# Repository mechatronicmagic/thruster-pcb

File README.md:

- [Repository Info](#orgcf761ff)
- [Images](#orga1b146e)
- [Schematic](#org2f8730d)
- [PCB](#orgee0fed7)
- [Bill of Materials](#org8738594)
- [Development](#org028dfc6)

    <!-- This file is generated automatically from metadata -->
    <!-- File edits may be overwritten! -->

# Repository Info

-   Project Name: thruster-pcb
-   Synopsis:
-   Documentation Version: 1.0.0
-   Pcb Version: 1.0
-   Enclosure Version: 1.0
-   Supplemental BOM Version: 1.0
-   Release Date: 2025-02-19
-   Creation Date: 2025-01-04
-   Kicad Version: 7.0.11
-   License: GPL-3.0h
-   URL: <https://github.com/mechatronicmagic/thruster-pcb>
-   Author: Peter Polidoro
-   Email: peter@polidoro.io
-   Copyright: 2025 Mechatronic Magic
-   References:
    -   [Servo Control](https://en.wikipedia.org/wiki/Servo_control)
    -   [SB2264MG Servo](https://www.savoxusa.com/products/savsb2264mg-low-profile-hv-brushless-servo)
    -   [PCA9685](https://www.nxp.com/products/power-management/lighting-driver-and-controller-ics/led-drivers/16-channel-12-bit-pwm-fm-plus-ic-bus-led-driver:PCA9685)
    -   [nRF52840 Express](https://www.adafruit.com/product/4062)

# Images

# Schematic

[./documentation/schematic/thruster-pcb.pdf](./documentation/schematic/thruster-pcb.pdf)

# PCB

# Bill of Materials

## Board

| Item | Synopsis                          | Manufacturer Part Number | Manufacturer                         | Quantity | Reference(s)                       | Package             |
|---- |--------------------------------- |------------------------ |------------------------------------ |-------- |---------------------------------- |------------------- |
| 1    | 50V 3.3uF                         | FS32X335K500EGG          | PSA(Prosperity Dielectrics)          | 1        | C301                               | 1210                |
| 2    | CAP CER 0.1UF 100V X5R            | GRM155R62A104KE14D       | Murata Electronics                   | 5        | C302 C401 C501 C502 C503           | 0402                |
| 3    | CAP CER 1UF 25V X5R               | GRT155R61E105KE01D       | Murata Electronics                   | 2        | C303 C304                          | 0402                |
| 4    | CAP CER 47UF 10V X5R              | CGA0805X5R476M100MT      | HRE                                  | 7        | C305 C504 C505 C506 C507 C508 C509 | 0805                |
| 5    | DIODE SCHOTTKY 20V 1A             | MBR120VLSFT1G            | onsemi                               | 1        | D401                               | SOD-123FL           |
| 6    | MAXIBR M 03POS RA A SMT BK        | 284052-E                 | TE Connectivity                      | 7        | J301 J501 J502 J503 J504 J505 J506 |                     |
| 7    | RES SMD 1.8K OHM 5% 100mW         | ERJ2GEJ182X              | PANASONIC                            | 2        | R401 R402                          | 0402                |
| 8    | 1 Digit SPST 24V 25mA DIP         | EM-01KP                  | Korean Hroparts Elec                 | 1        | SW401                              | SMD,2.5x6mm         |
| 9    | DC-DC 5V 600mA Output 3-65V Input | TPSM365R6V5RDNR          | Texas Instruments                    | 1        | U301                               | QFN-11(3.5x4.5)     |
| 10   | IC SWITCH DEBOUNCER               | MAX6816EUS+T             | Analog Devices Inc./Maxim Integrated | 1        | U401                               | SOT-143             |
| 11   | IC LED DRVR LIN PWM 25MA          | PCA9685BS,118            | NXP Semicon                          | 1        | U501                               | SOT-788-1           |
| 12   | IC TRANSLTR BIDIRECTIONAL         | TXS0108ERGYR             | Texas Instruments                    | 1        | U502                               | VQFN-20-EP(3.7x4.7) |

## Supplemental

| Item | Synopsis                                                            | Manufacturer Part Number | Manufacturer | Quantity | Cost  | Total |
|---- |------------------------------------------------------------------- |------------------------ |------------ |-------- |----- |----- |
| 1    | Adafruit Feather nRF52840 Express                                   | 4062                     | adafruit     | 1        | 24.95 | 24.95 |
| 2    | NiMH Battery (6V, 2700mAh, 2-Pos TJC8 Power Connector [MH-FC], 6-1) | 3100-0006-0001           | servocity    | 1        | 14.99 | 14.99 |
|      | Supplemental BOM Version: 1.0                                       |                          |              |          | Total | 39.94 |

# Development

## Install Guix

[Install Guix](https://guix.gnu.org/manual/en/html_node/Binary-Installation.html)

## Generate Output from KiCad

### Remove previous versions

```sh
rm -rf ./documentation/3dmodels/* && rm -rf ./documentation/bom/* && rm -rf ./documentation/fabrication/* && rm -rf ./documentation/pcb/* && rm -rf ./documentation/schematic/*pcb
```

### Images

1.  3D Viewer

    Output directory: ../documentation/pcb
    
    -   pcb.png
    -   top.png
    -   bottom.png
    -   front.png
    -   back.png
    -   left.png
    -   right.png

2.  Trim

        make trimmed-images

3.  Schematic PDF

    File -> Plot
    
    Output directory: ../documentation/schematic
    
    Plot All Pages
    
    -   Output format PDF
    -   Page Size = Schematic size
    -   Plot drawing sheet
    -   Output mode = Color
    -   Color theme = KiCad Default
    -   Default line width = 0.006 in

4.  Schematic SVG

    File -> Plot
    
    Output directory: ../documentation/schematic
    
    Plot All Pages
    
    -   Output format SVG
    -   Page Size = Schematic size
    -   Plot drawing sheet
    -   Output mode = Color
    -   Color theme = Solarized Light
    -   Default line width = 0.012 in

5.  PCB SVG

    Add Edge.Cuts, holes, and dimensions to User.Drawings
    
    File -> Plot
    
    Output directory: ../documentation/pcb
    
    -   Plot format SVG
    -   Include Layers
        -   User.Drawings
        -   F.Silkscreen
        -   B.Silkscreen
        -   F.Fab
        -   B.Fab
    -   Plot on All Layers
        -   Edge.Cuts
    -   Plot footprint values
    -   Plot reference designators
    -   SVG Options
        -   Precision = 4
        -   Output mode = color
    
        make cropped-svg

### Fabrication Files

1.  Gerbers

    File -> Fabrication Outputs -> Gerbers (.gbr)
    
    Output directory: ../documentation/fabrication/gerbers
    
    Include Layers:
    
    -   F.Cu
    -   F.Paste
    -   F.Silks
    -   F.Mask
    -   F.Fab
    -   B.Cu
    -   B.Paste
    -   B.Silks
    -   B.Mask
    -   B.Fab
    -   Edge.Cuts - (contain the board outline/cutouts.)
    -   In1.Cu, In2.Cu … - (needed for 4/6 layer designs.)
    
    Options:
    
    -   Select Plot reference designators, otherwise designators will not appear on silkscreen layers.
    -   Select Check zone fills before plotting
    -   Select Use Protel filename extensions, this is recommended as JLCPCB prefers Protel filename extensions.
    -   Select Subtract soldermask from silkscreen, this ensures no silkscreen on pads.
    -   Coordinate format 4.6 unit mm

2.  Drill and Map Files

    Output directory: ../documentation/fabrication/gerbers
    
    Options:
    
    -   Excellon drill file format
    -   Check Use alternate drill mode for "Oval Holes Drill Mode".
    -   Check Absolute for "Drill Origin".
    -   Check Millimeters for "Drill Units".
    -   Check Decimal format for "Zeros Format".
    -   Gerber X2 map file format
    
    Zip gerber files
    
        zip ./documentation/fabrication/gerbers.zip ./documentation/fabrication/gerbers/*

3.  BOM

    Generate BOM from schematic editor using blank command line to create bom xml file.

4.  POS

    File -> Fabrication Outputs -> Component Placement (.pos)
    
    Output directory: ../documentation/fabrication/
    
    Settings:
    
    -   Format = CSV
    -   Units = Millimeters
    -   Files = Single file for board
    -   Do not use drill/place file origin
    
    Modify pos files:
    
    -   Ref -> Designator
    -   PosX -> Mid X
    -   PosY -> Mid Y
    -   Rot -> Rotation
    -   Side -> Layer

5.  Step

    File -> Export -> Step
    
    Output directory: ../documentation/3dmodels/pcb.step
    
    -   Drill/place file origin
    -   Overwrite old file
    -   Standard Board outline chaining tolerance

## Edit metadata.org

    make metadata-edits

## Tangle metadata.org

    make metadata

## Edit project

    make kicad-edits
    exit

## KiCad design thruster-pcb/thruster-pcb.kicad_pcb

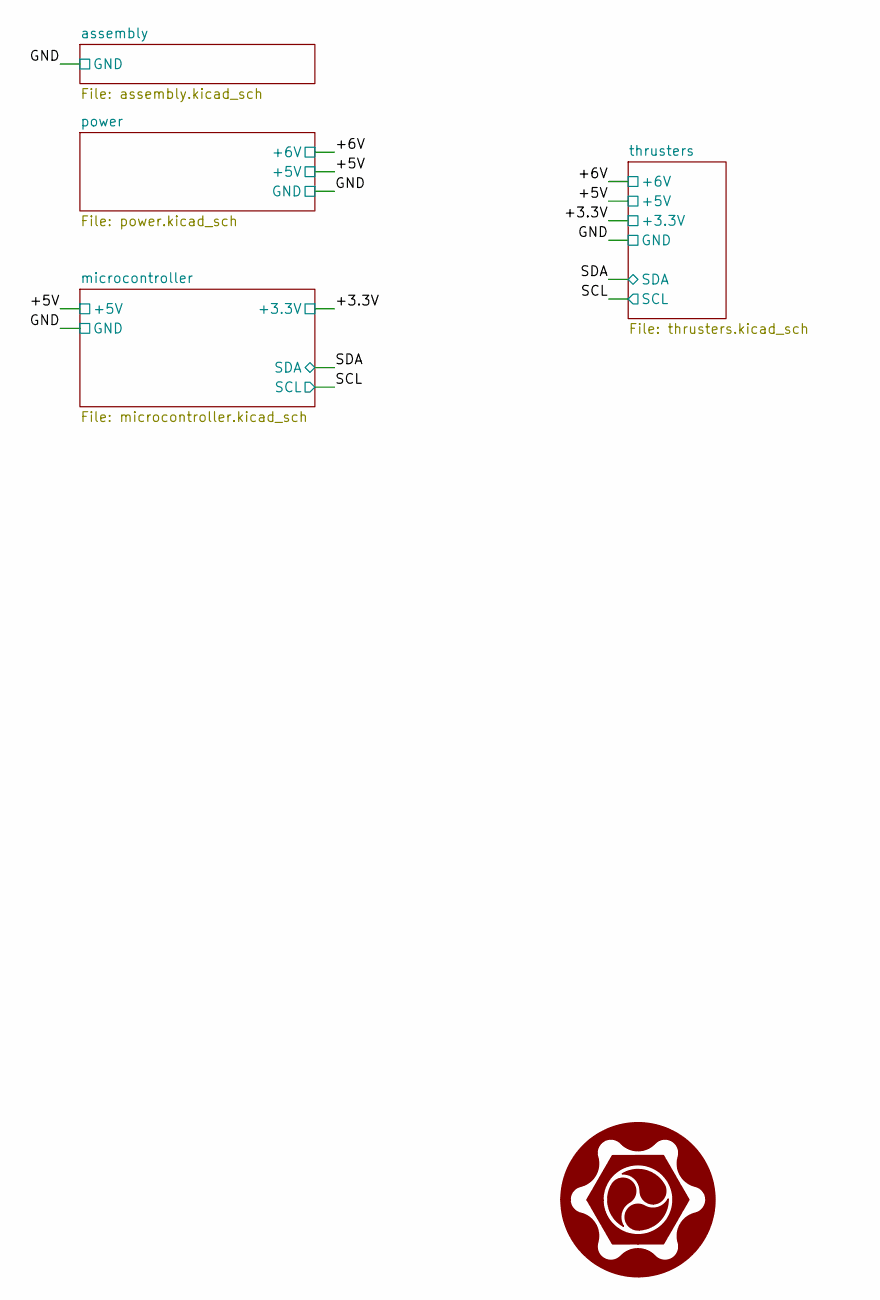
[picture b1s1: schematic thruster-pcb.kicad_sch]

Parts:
G101: LOGO-10mm; logo-white-fg-black-bg-10mm

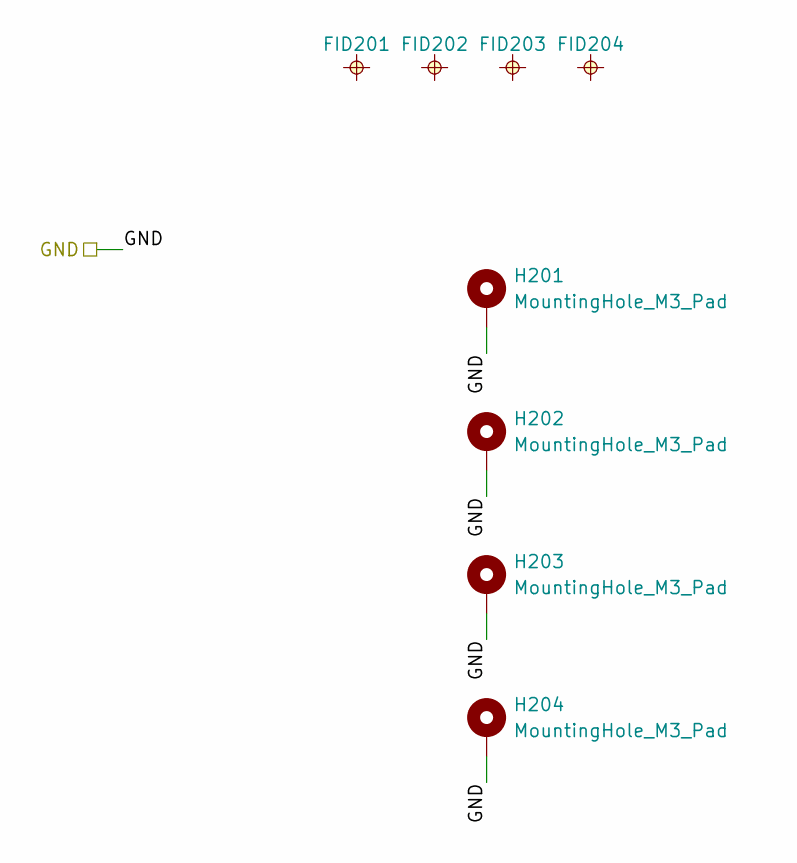
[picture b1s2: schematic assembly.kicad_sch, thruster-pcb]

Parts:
FID201, FID202, FID203, FID204: FIDUCIAL_0.5mm_MASK1mm; FIDUCIAL_0.5mm_Mask1mm
H201, H202, H203, H204: MountingHole_M3_Pad; MountingHole_3.2mm_M3_Pad

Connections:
/GND: H201.1, H202.1, H203.1, H204.1; also elsewhere on the board

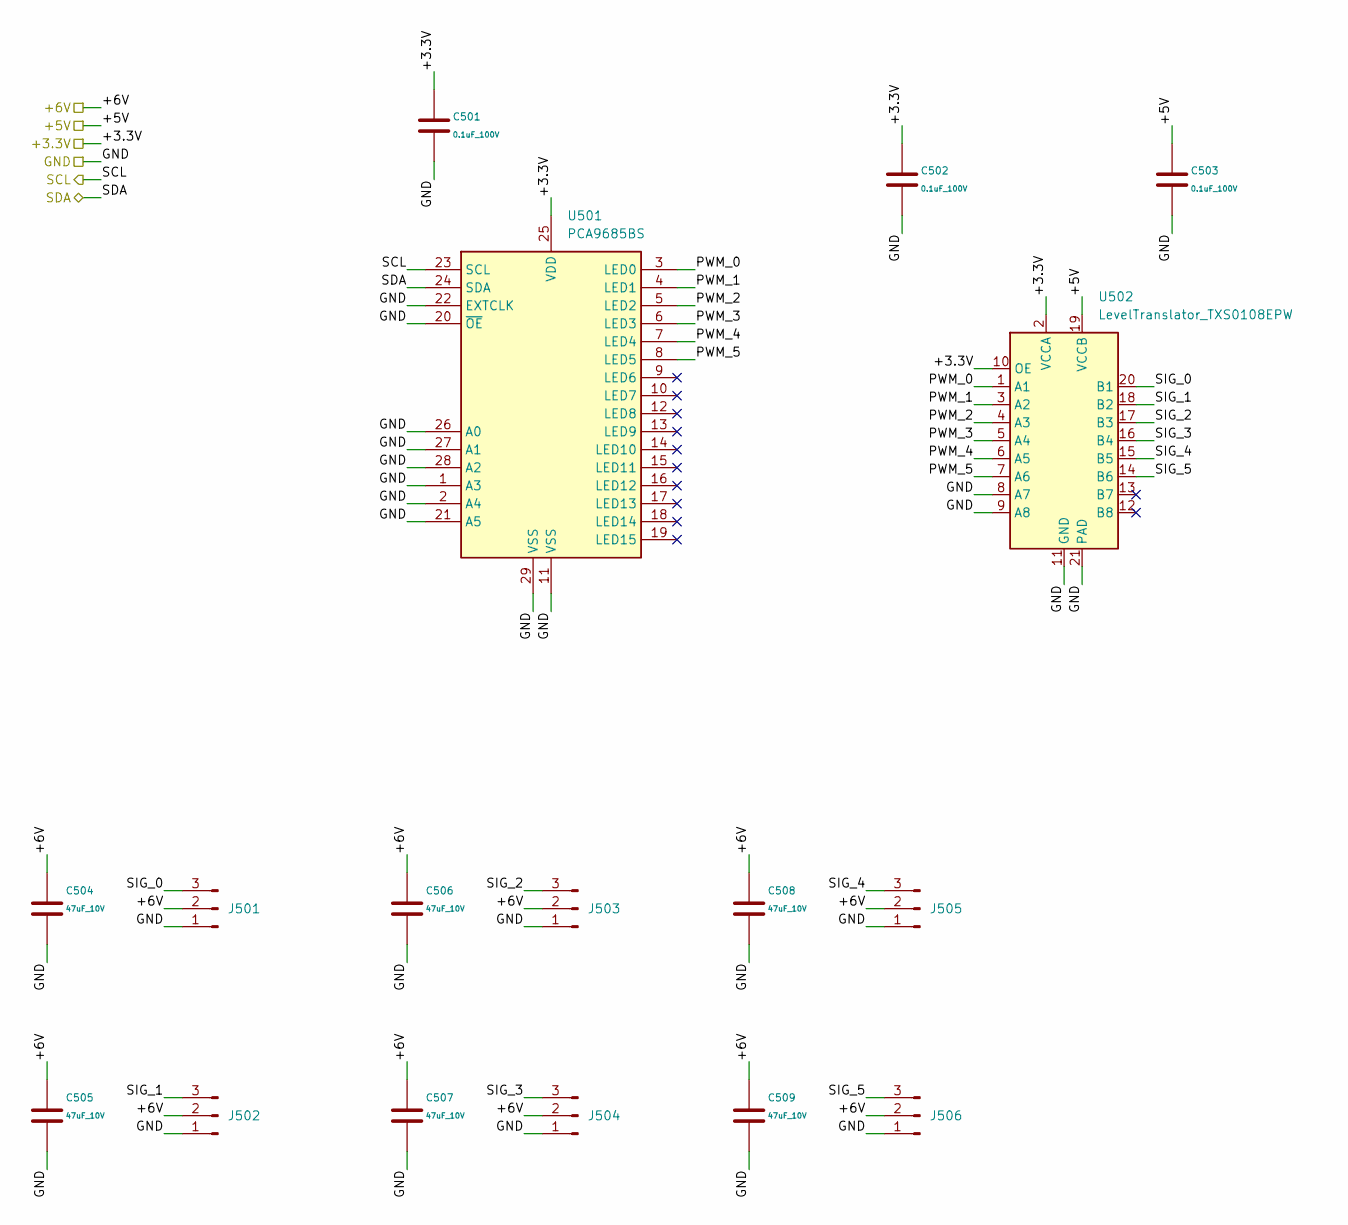
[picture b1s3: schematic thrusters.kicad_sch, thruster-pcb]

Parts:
C501, C502, C503: 0.1uF_100V; C_0402_1005Metric; Manufacturer Part Number GRM155R62A104KE14D; LCSC C162178
C504, C505, C506, C507, C508, C509: 47uF_10V; C_0805_2012Metric; Manufacturer Part Number CGA0805X5R476M100MT; LCSC C6119904
J501, J502, J503, J504, J505, J506: Conn_TERM_HDR_01x03_Pin_3.5mm_Horizontal; Connector_Header_1x03_P2.54mm_Horizontal_SMD_284052-E; Manufacturer Part Number 284052-E; LCSC C17355078
U501: PCA9685BS; QFN-28-1EP_6x6mm_P0.65mm_EP4.25x4.25mm; Manufacturer Part Number PCA9685BS,118; LCSC C5191634
U502: LevelTranslator_TXS0108EPW; IC_TXS0108ERGYR; Manufacturer Part Number TXS0108ERGYR; LCSC C90706

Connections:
/+3.3V: C501.1, C502.1, U501.25 (VDD), U502.2 (VCCA), U502.10 (OE); also elsewhere on the board
/+5V: C503.1, U502.19 (VCCB); also elsewhere on the board
/+6V: C504.1, C505.1, C506.1, C507.1, C508.1, C509.1, J501.2, J502.2, J503.2, J504.2, J505.2, J506.2; also elsewhere on the board
/GND: C501.2, C502.2, C503.2, C504.2, C505.2, C506.2, C507.2, C508.2, C509.2, J501.1, J502.1, J503.1, J504.1, J505.1, J506.1, U501.1 (A3), U501.2 (A4), U501.11 (VSS), U501.20 (~OE), U501.21 (A5), U501.22 (EXTCLK), U501.26 (A0), U501.27 (A1), U501.28 (A2), U501.29 (VSS), U502.8 (A7), U502.9 (A8), U502.11 (GND), U502.21 (PAD); also elsewhere on the board
/SCL: U501.23 (SCL); also elsewhere on the board
/SDA: U501.24 (SDA); also elsewhere on the board
/thrusters/PWM_0: U501.3 (LED0), U502.1 (A1)
/thrusters/PWM_1: U501.4 (LED1), U502.3 (A2)
/thrusters/PWM_2: U501.5 (LED2), U502.4 (A3)
/thrusters/PWM_3: U501.6 (LED3), U502.5 (A4)
/thrusters/PWM_4: U501.7 (LED4), U502.6 (A5)
/thrusters/PWM_5: U501.8 (LED5), U502.7 (A6)
/thrusters/SIG_0: J501.3, U502.20 (B1)
/thrusters/SIG_1: J502.3, U502.18 (B2)
/thrusters/SIG_2: J503.3, U502.17 (B3)
/thrusters/SIG_3: J504.3, U502.16 (B4)
/thrusters/SIG_4: J505.3, U502.15 (B5)
/thrusters/SIG_5: J506.3, U502.14 (B6)

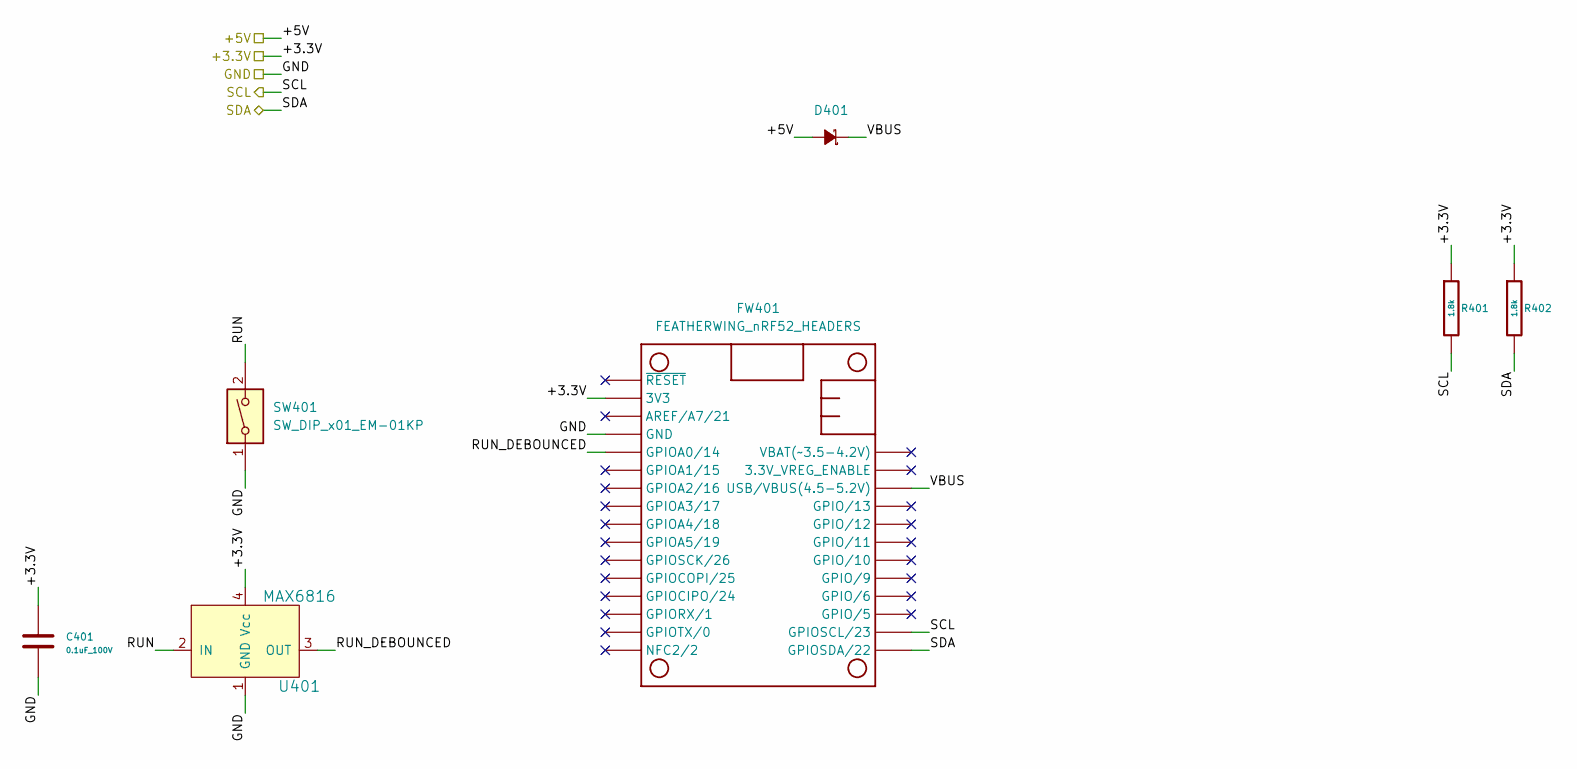
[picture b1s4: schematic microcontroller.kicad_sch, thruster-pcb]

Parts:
C401: 0.1uF_100V; C_0402_1005Metric; Manufacturer Part Number GRM155R62A104KE14D; LCSC C162178
D401: D_SCHOTTKY_20V_1A; SOD-123FL; Manufacturer Part Number MBR120VLSFT1G; LCSC C223608
FW401: FEATHERWING_nRF52_HEADERS; FEATHERWING_HEADERS; Manufacturer Part Number 4062
R401, R402: 1.8k; R_0402_1005Metric; Manufacturer Part Number ERJ2GEJ182X; LCSC C409855
SW401: SW_DIP_x01_EM-01KP; SW_SPST_EM-01KP; Manufacturer Part Number EM-01KP; LCSC C129077
U401: MAX6816; SOT192P237X122-4N; Manufacturer Part Number MAX6816EUS+T; LCSC C41637

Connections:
/+3.3V: C401.1, FW401.2 (3V3), R401.1, R402.1, U401.4 (Vcc); also elsewhere on the board
/+5V: D401.2 (A); also elsewhere on the board
/GND: C401.2, FW401.4 (GND), SW401.1, U401.1 (GND); also elsewhere on the board
/SCL: FW401.18 (GPIOSCL/23), R401.2; also elsewhere on the board
/SDA: FW401.17 (GPIOSDA/22), R402.2; also elsewhere on the board
/microcontroller/RUN: SW401.2, U401.2 (IN)
/microcontroller/RUN_DEBOUNCED: FW401.5 (GPIOA0/14), U401.3 (OUT)
/microcontroller/VBUS: D401.1 (K), FW401.26 (USB/VBUS(4.5-5.2V))

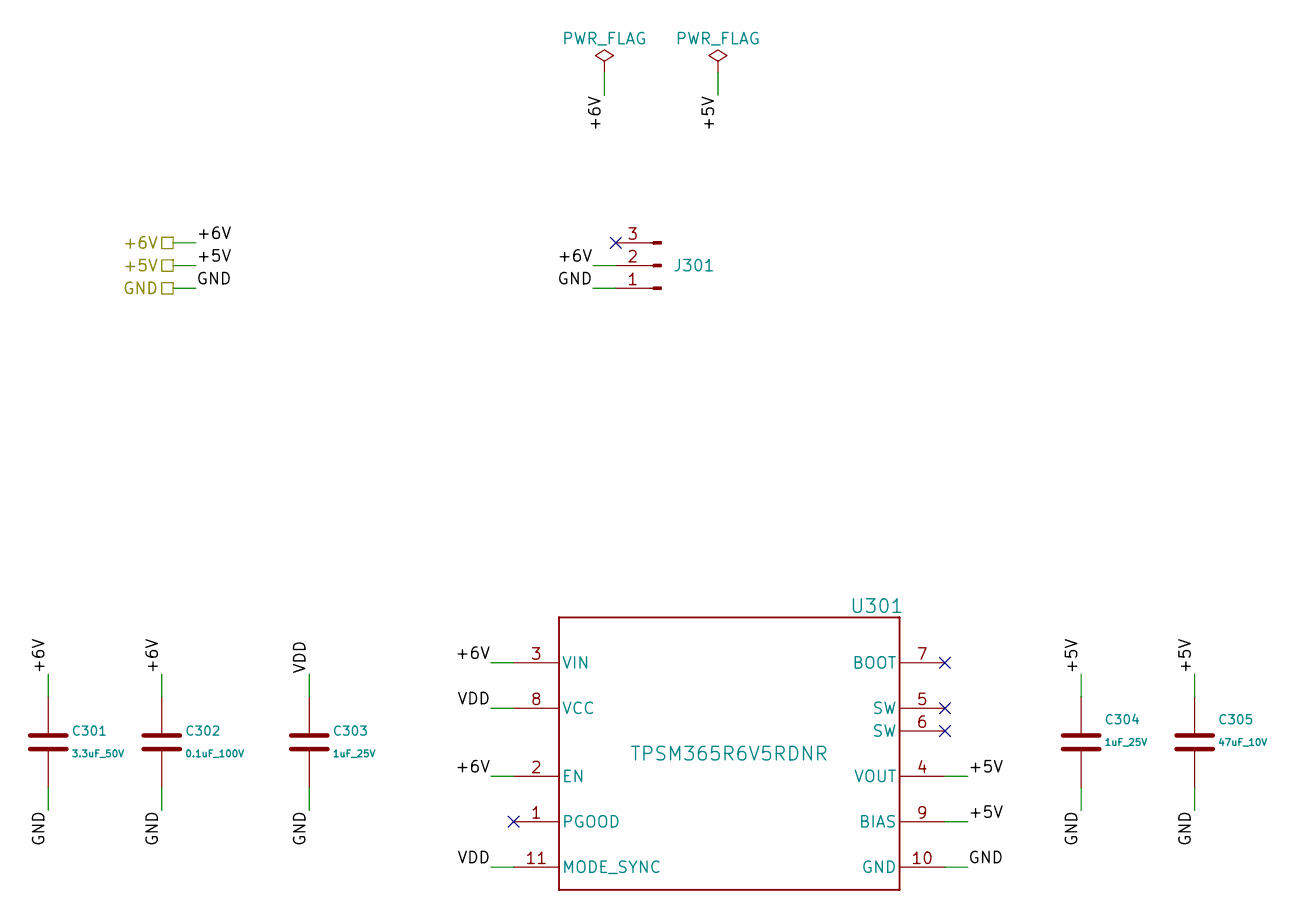
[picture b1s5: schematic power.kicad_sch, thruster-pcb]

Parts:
C301: 3.3uF_50V; C_1210_3225Metric; Manufacturer Part Number FS32X335K500EGG; LCSC C1021610
C302: 0.1uF_100V; C_0402_1005Metric; Manufacturer Part Number GRM155R62A104KE14D; LCSC C162178
C303, C304: 1uF_25V; C_0402_1005Metric; Manufacturer Part Number GRT155R61E105KE01D; LCSC C711085
C305: 47uF_10V; C_0805_2012Metric; Manufacturer Part Number CGA0805X5R476M100MT; LCSC C6119904
J301: Conn_TERM_HDR_01x03_Pin_3.5mm_Horizontal; Connector_Header_1x03_P2.54mm_Horizontal_SMD_284052-E; Manufacturer Part Number 284052-E; LCSC C17355078
U301: TPSM365R6V5RDNR; RDN0011A-MFG; Manufacturer Part Number TPSM365R6V5RDNR; LCSC C19078014

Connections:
/+5V: C304.1, C305.1, U301.4 (VOUT), U301.9 (BIAS); also elsewhere on the board
/+6V: C301.1, C302.1, J301.2, U301.2 (EN), U301.3 (VIN); also elsewhere on the board
/GND: C301.2, C302.2, C303.2, C304.2, C305.2, J301.1, U301.10 (GND); also elsewhere on the board
/power/VDD: C303.1, U301.8 (VCC), U301.11 (MODE_SYNC)

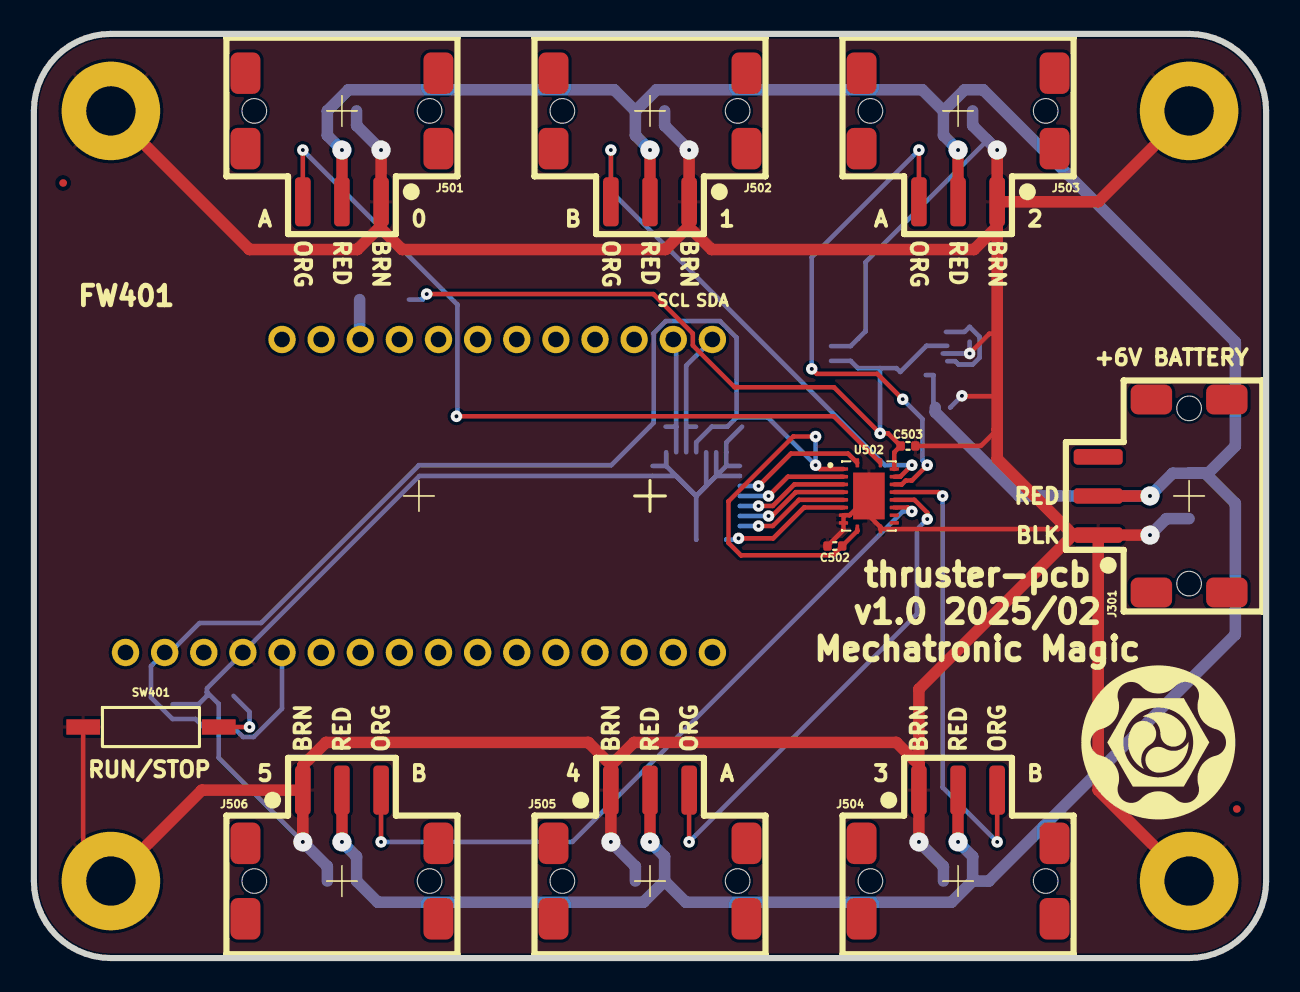
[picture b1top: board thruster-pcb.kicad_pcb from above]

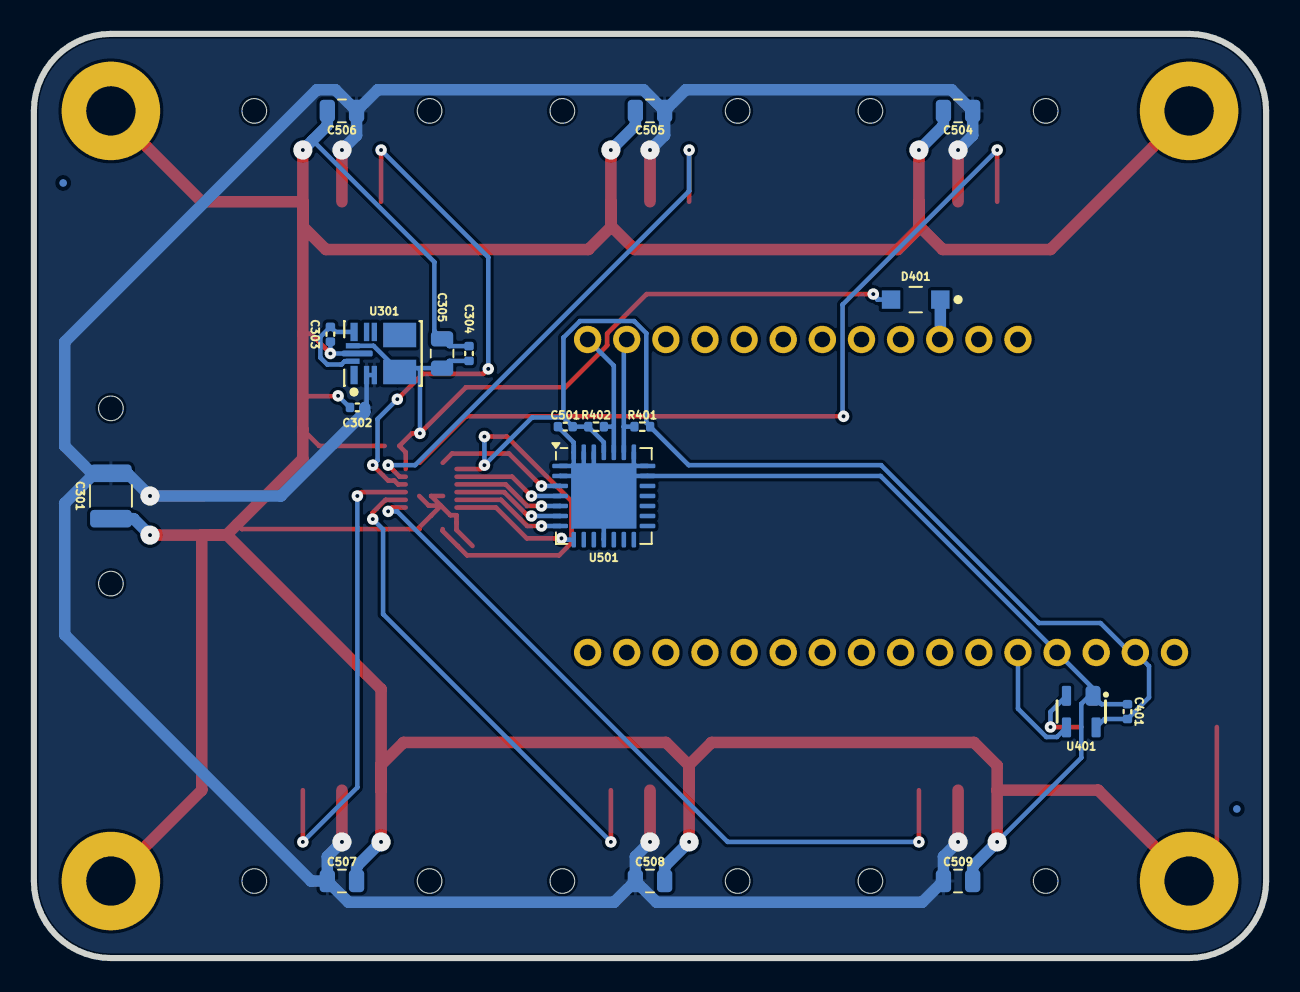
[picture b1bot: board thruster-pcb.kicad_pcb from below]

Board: 2 copper layers, 80.0 x 60.0 mm, 40 parts (21 on the bottom side), 22 nets.

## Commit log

2025-01-04 tmc5160-usb -> thruster-pcb
2025-01-04 Add reference files
2025-01-12 Add parts to schematic
2025-02-16 Use PCA9685 and nRF52
2025-02-17 Initial components
2025-02-17 Add sheets
2025-02-18 Initial schematic and layout
2025-02-19 Initial layout
2025-02-19 Finished v1.0
2025-02-19 Updated pcb
2025-02-19 Updated supplemental-bom
2025-02-19 Add bom
